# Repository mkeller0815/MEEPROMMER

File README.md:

MEEPROMMER
==========

(E)EPROM programmer based on Arduino hardware

The MEEPROMMER is a combination of hardware and software that lets you read and write 
data from (and to) 28Cxxx EEPROMS. Maybe later there will be enhancements to use it
also for 27Cxxx EPROMS. 

At the moment we have an working prototype on a PCB that uses an Arduino Nano and an 
Arduino-shield that can directly plugged to an Arduino Uno. 

The Arduino firmware provides a serial interface with simple commands to transfer data 
between a host computer and an eeprom.

For the host computer a Java based GUI application is available that uses the RXTX 
library to interface the programmer.

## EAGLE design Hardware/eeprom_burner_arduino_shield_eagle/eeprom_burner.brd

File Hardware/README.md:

this folder contain the hardware related files

The PCB is available at: https://www.tindie.com/products/UnaClocker/28cxxx-eeprom-programmer-shield-for-arduino/

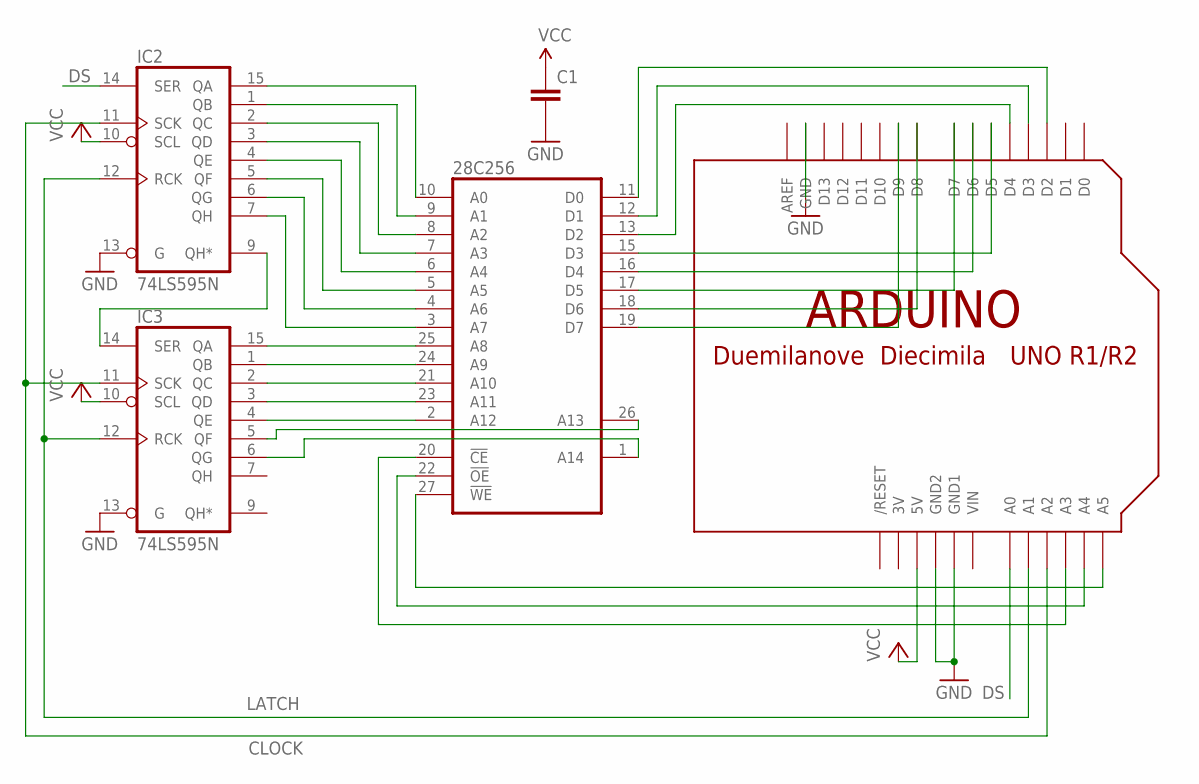
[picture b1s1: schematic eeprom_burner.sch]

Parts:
28C256: 2864; DIL28
C1: CAPPTH; CAP-PTH-SMALL
IC2, IC3: 74LS595N; DIL16
U$1: ARDUINOUNO; ARDUINO

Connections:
3V: U$1.3V
CLOCK: IC2.11 (SCK), IC3.11 (SCK), U$1.A2
DS: IC2.14 (SER), U$1.A0
GND: 28C256.14 (GND), C1.2, IC2.8 (GND), IC2.13 (G), IC3.8 (GND), IC3.13 (G), U$1.GND, U$1.GND1, U$1.GND2
LATCH: IC2.12 (RCK), IC3.12 (RCK), U$1.A1
unnamed: 28C256.27 (!WE), U$1.A5
unnamed: 28C256.22 (!OE), U$1.A4
unnamed: 28C256.20 (!CE), U$1.A3
unnamed: 28C256.11 (D0), U$1.D2
unnamed: 28C256.12 (D1), U$1.D3
unnamed: 28C256.13 (D2), U$1.D4
unnamed: 28C256.15 (D3), U$1.D5
unnamed: 28C256.16 (D4), U$1.D6
unnamed: 28C256.17 (D5), U$1.D7
unnamed: 28C256.18 (D6), U$1.D8
unnamed: 28C256.19 (D7), U$1.D9
unnamed: 28C256.10 (A0), IC2.15 (QA)
unnamed: 28C256.9 (A1), IC2.1 (QB)
unnamed: 28C256.8 (A2), IC2.2 (QC)
unnamed: 28C256.7 (A3), IC2.3 (QD)
unnamed: 28C256.6 (A4), IC2.4 (QE)
unnamed: 28C256.5 (A5), IC2.5 (QF)
unnamed: 28C256.4 (A6), IC2.6 (QG)
unnamed: 28C256.3 (A7), IC2.7 (QH)
unnamed: IC2.9 (QH*), IC3.14 (SER)
unnamed: 28C256.25 (A8), IC3.15 (QA)
unnamed: 28C256.24 (A9), IC3.1 (QB)
unnamed: 28C256.21 (A10), IC3.2 (QC)
unnamed: 28C256.23 (A11), IC3.3 (QD)
unnamed: 28C256.2 (A12), IC3.4 (QE)
unnamed: 28C256.26 (A13), IC3.5 (QF)
unnamed: 28C256.1 (A14), IC3.6 (QG)
VCC: 28C256.28 (VCC), C1.1, IC2.10 (SCL), IC2.16 (VCC), IC3.10 (SCL), IC3.16 (VCC), U$1.5V
VIN: U$1.VIN

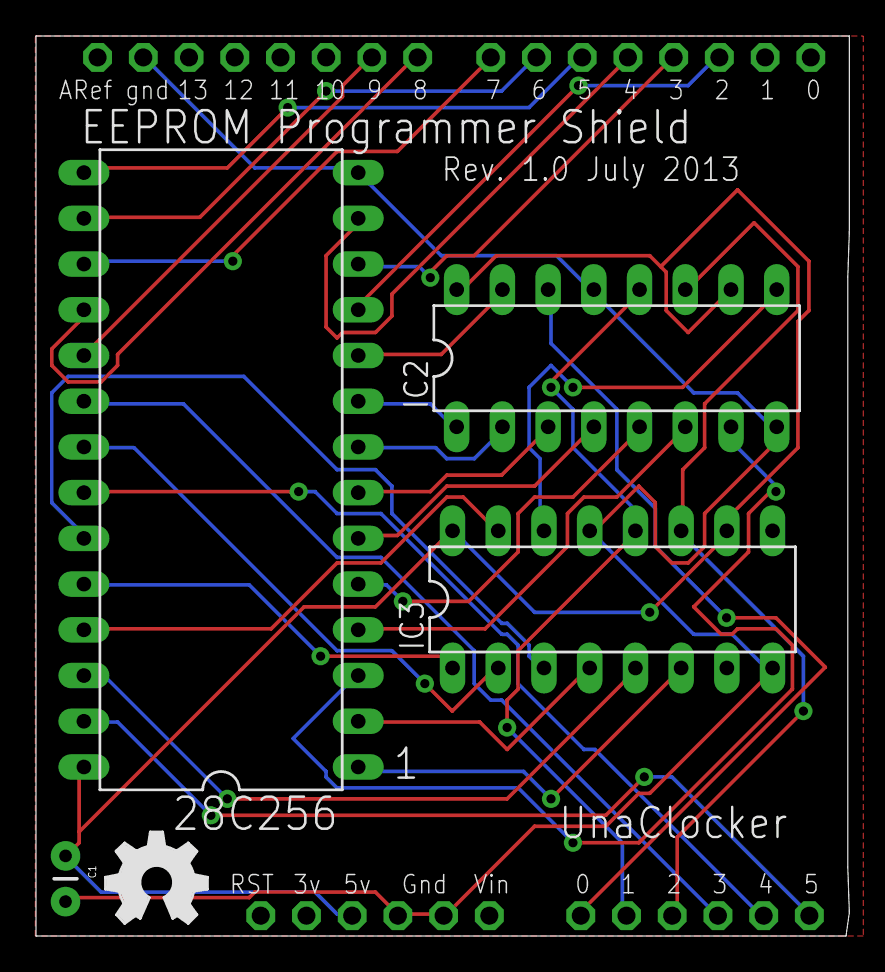
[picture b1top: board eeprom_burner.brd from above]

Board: 2 copper layers, 45.2 x 50.0 mm, 7 parts (1 on the bottom side), 32 nets.

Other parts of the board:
U$2, U$3: OSHW_FILLX200_NOTEXT

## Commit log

2013-07-29 Update README.md
    added additional information, fixed typos.
2013-07-29 initial source commit
2013-07-29 removed DS_Store
2013-07-29 added additional folders
2013-07-29 Replaced output to log window with a generic function in all methods of MainFrame.java
2013-07-30 gitignore adjusted
2013-07-30 added additional files
2013-07-30 moved java source to own folder to cleanup project structure
2013-07-30 deleted old files
2013-07-30 adjsutes gitignore to match new java source folder
2013-08-13 adjustes serial speed to 115200 and added link to PCB on tindie.com
2013-11-22 CMD list in version string corrected; matches parseCommand().
    `parseCommand()` defines commands as:
    ```
    R: READ_HEX
    r: READ_BIN
    W: WRITE_HEX
    w: WRITE_BIN
2013-11-22 New 'A,0000' command sets address bus to given value.
    Useful for debugging shift-register wiring and the resulting address bus
    byte order.
    e.g. `A,00FF` should only set A0..A7 high.
2013-11-22 Shift high byte of address bus first.
    The schematic at http://www.ichbinzustaendig.de/dev/meeprommer-en shows
    the low-byte address bus 74HC595 (EEPROM A0..A7) connected first,
    cascading into the high-byte 74HC595. This means the high byte should be
    shifted first. The code comments reflect this, but the actual code
    doesn't.
    Note that @presslab-us's fork shifts the high byte first, although he
2014-01-04 Python CLI, Paged Write, Unlocker
    Fleshed out python command line interface
    Added paged write and unlock functions
2014-01-05 Put back JBurn for pull request
2014-04-02 serial connection set to 115200 baud simple improvements for java gui
2014-04-02 added binary jar file for simple use via github
2014-06-12 new build
2014-06-12 added swing-layout-1.0.4.jar to bin repo
2018-05-24 fixed pinout of Arduino nano in prototype_schema.jpg

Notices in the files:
parts and their libraries:
SparkFun: Licensing: CC v3.0 Share-Alike You are welcome to use this library for commercial purposes.
